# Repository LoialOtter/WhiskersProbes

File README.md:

# WhiskersProbes
A set of low cost probes for logic analyzers and oscilloscopes.

## Whiskers-DigitalProbe

The logic probe is aiming to be a 500MHz+ Differential buffer to single ended for using a logic analyzer on LVDS signals.

Of note, the matching network on the output is to allow you to match the circuit directly to your logic analyzer input. The values shown in the schematic are the ones needed for HP/Agilent/Keysight if you're using ribbon cables. If you're using a logic analyzer input, the capacitors should not be placed and the resistors should be 0 ohm.

## Whiskers-AnalogProbe
Coming soon

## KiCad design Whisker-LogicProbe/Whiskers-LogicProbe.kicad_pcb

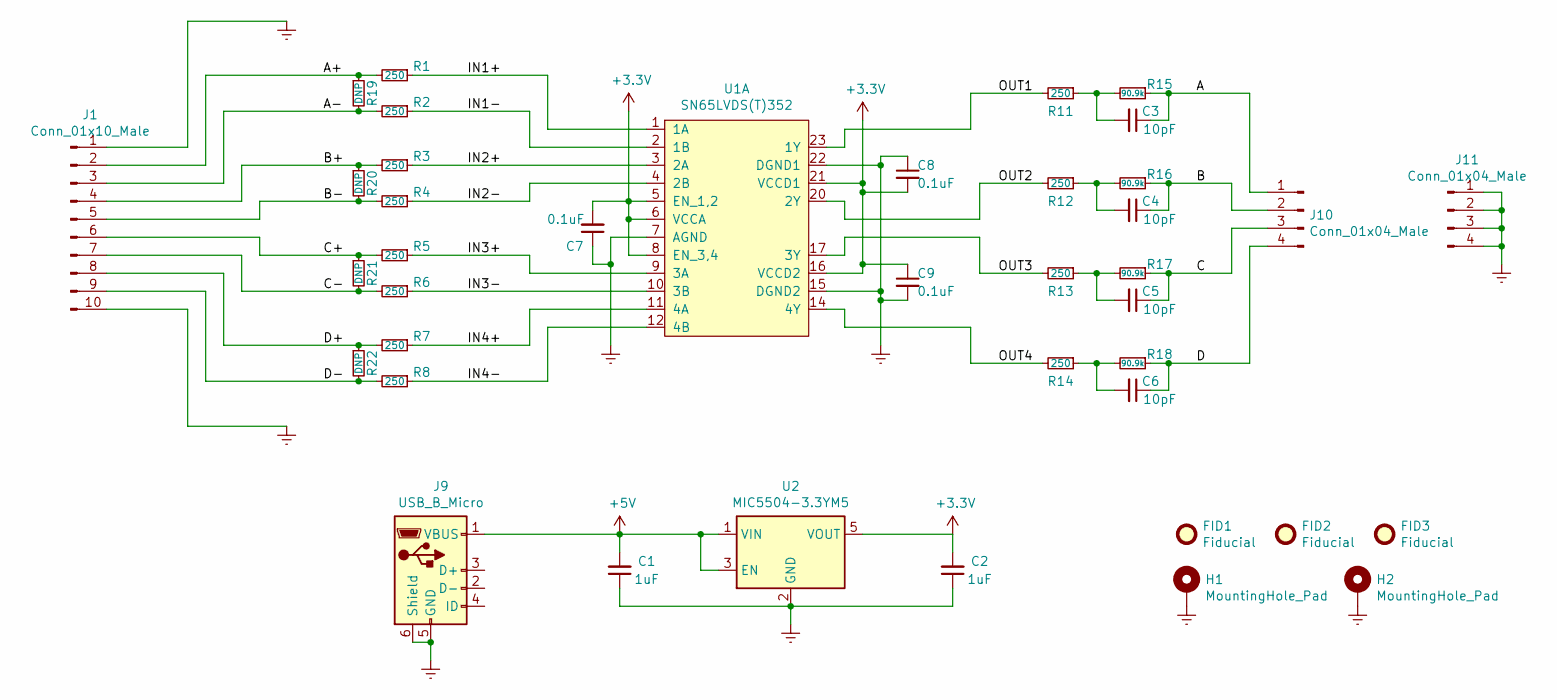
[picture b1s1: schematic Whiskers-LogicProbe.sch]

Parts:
C1, C2: 1uF; C_0603_1608Metric
C3, C4, C5, C6: 10pF; C_0603_1608Metric
C7, C8, C9: 0.1uF; C_0603_1608Metric
FID1, FID2, FID3: Fiducial; Fiducial_0.5mm_Mask1mm
H1, H2: MountingHole_Pad; MountingHole_3.2mm_M3_DIN965_Pad
J1: Conn_01x10_Male; PinHeader_1x10_P2.54mm_Vertical
J9: USB_B_Micro; USB_Micro-B_GCT_USB3076-30-A
J10: Conn_01x04_Male; PinHeader_1x04_P2.54mm_Vertical
J11: Conn_01x04_Male; PinHeader_1x04_P2.54mm_Horizontal
R1, R2, R3, R4, R5, R6, R7, R8, R11, R12, R13, R14: 250; R_0603_1608Metric
R15, R16, R17, R18: 90.9k; R_0603_1608Metric
R19, R20, R21, R22: DNP; R_0603_1608Metric
U1: SN65LVDS(T)352; TSSOP-24_4.4x7.8mm_P0.65mm; Digikey 296-12649-5-ND
U2: MIC5504-3.3YM5; SOT-23-5

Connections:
+3V3: C2.2, C7.2, C8.2, C9.1, U1.5 (EN_1,2), U1.6 (VCCA), U1.8 (EN_3,4), U1.16 (VCCD2), U1.21 (VCCD1), U2.5 (VOUT)
+5V: C1.2, J9.1 (VBUS), U2.1 (VIN), U2.3 (EN)
/A: C3.1, J10.1, R15.1
/A+: J1.2, R1.2, R19.1
/A-: J1.3, R2.2, R19.2
/B: C4.1, J10.2, R16.1
/B+: J1.4, R3.2, R20.1
/B-: J1.5, R4.2, R20.2
/C: C5.1, J10.3, R17.1
/C+: J1.6, R5.2, R21.1
/C-: J1.7, R6.2, R21.2
/D: C6.1, J10.4, R18.1
/D+: J1.8, R7.2, R22.1
/D-: J1.9, R8.2, R22.2
/IN1+: R1.1, U1.1 (1A)
/IN1-: R2.1, U1.2 (1B)
/IN2+: R3.1, U1.3 (2A)
/IN2-: R4.1, U1.4 (2B)
/IN3+: R5.1, U1.9 (3A)
/IN3-: R6.1, U1.10 (3B)
/IN4+: R7.1, U1.11 (4A)
/IN4-: R8.1, U1.12 (4B)
/OUT1: R11.2, U1.23 (1Y)
/OUT2: R12.2, U1.20 (2Y)
/OUT3: R13.2, U1.17 (3Y)
/OUT4: R14.2, U1.14 (4Y)
GNDREF: C1.1, C2.1, C7.1, C8.1, C9.2, H1.1, H2.1, J1.1, J1.10, J9.5 (GND), J9.6 (Shield), J11.1, J11.2, J11.3, J11.4, U1.7 (AGND), U1.15 (DGND2), U1.22 (DGND1), U2.2 (GND)
unnamed: C3.2, R11.1, R15.2
unnamed: C4.2, R12.1, R16.2
unnamed: C5.2, R13.1, R17.2
unnamed: C6.2, R14.1, R18.2

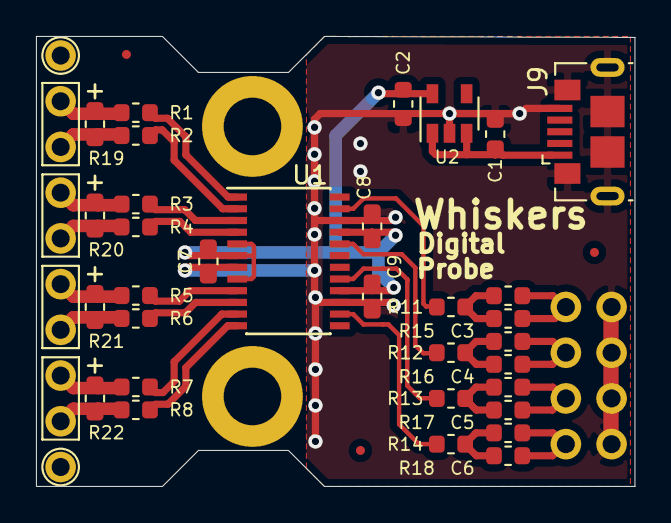
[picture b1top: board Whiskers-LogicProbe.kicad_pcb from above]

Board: 2 copper layers, 33.2 x 25.0 mm, 40 parts (1 on the bottom side), 31 nets.

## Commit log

2021-02-06 Initial import of logic probe design
2021-02-06 Import of actual files.
2021-02-06 Updated to use the proper LVDS receiver chip (560Mb/s one)
2021-02-06 Added PDF and updated README
